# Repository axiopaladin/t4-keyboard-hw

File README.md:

# T4 Keyboard Hardware
This is a repository that contains Kicad files for devices that attach to the dock connector on
a LincPlus T4 tablet.

The first hardware will be a simple breakout board, designed to help enumerate the pins properly.

Future projects aim to integrate a full keyboard for this device, as LincPlus seems to have
abandoned the product line, despite continuing to sell it in several markets.

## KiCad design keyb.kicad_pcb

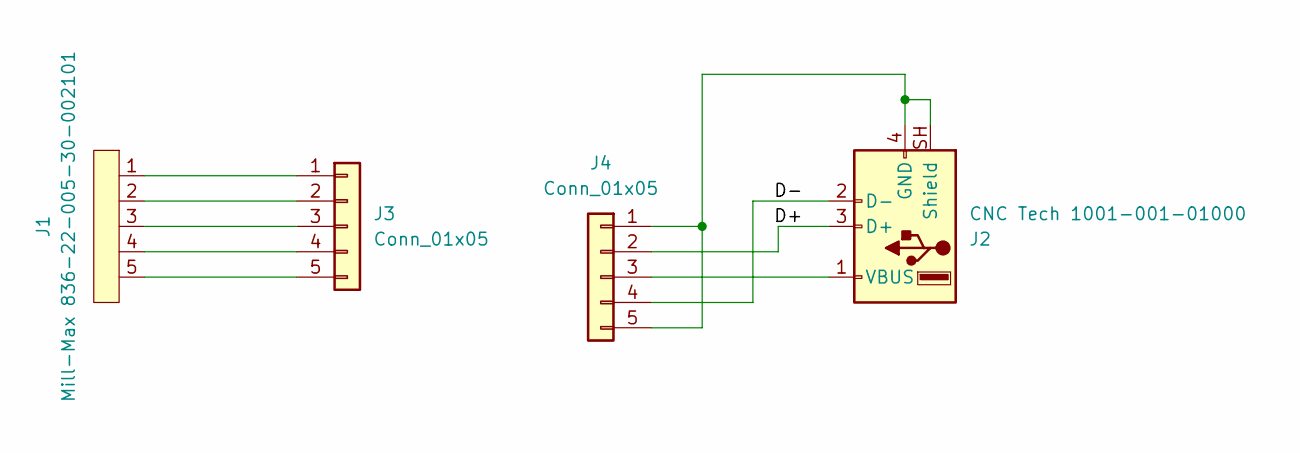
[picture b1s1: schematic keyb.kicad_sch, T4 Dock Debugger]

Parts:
J1: Mill-Max 836-22-005-30-002101; Mill-Max_836-22-005-30-002101
J2: CNC Tech 1001-001-01000; USB_A_Stewart_SS-52100-001_Horizontal
J3, J4: Conn_01x05; PinSocket_1x05_P2.54mm_Vertical

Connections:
/D+: J2.3 (D+), J4.2
/D-: J2.2 (D-), J4.4
unnamed: J2.4 (GND), J2.SH (Shield), J4.1, J4.5
unnamed: J2.1 (VBUS), J4.3
unnamed: J1.1, J3.1
unnamed: J1.2, J3.2
unnamed: J1.3, J3.3
unnamed: J1.4, J3.4
unnamed: J1.5, J3.5

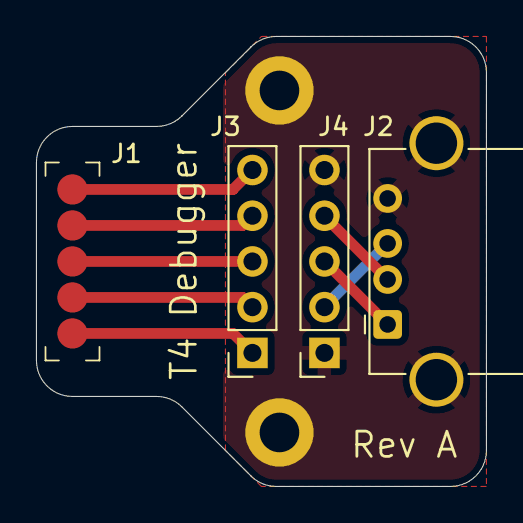
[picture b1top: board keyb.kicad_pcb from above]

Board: 2 copper layers, 25.0 x 25.0 mm, 4 parts (0 on the bottom side), 9 nets.
